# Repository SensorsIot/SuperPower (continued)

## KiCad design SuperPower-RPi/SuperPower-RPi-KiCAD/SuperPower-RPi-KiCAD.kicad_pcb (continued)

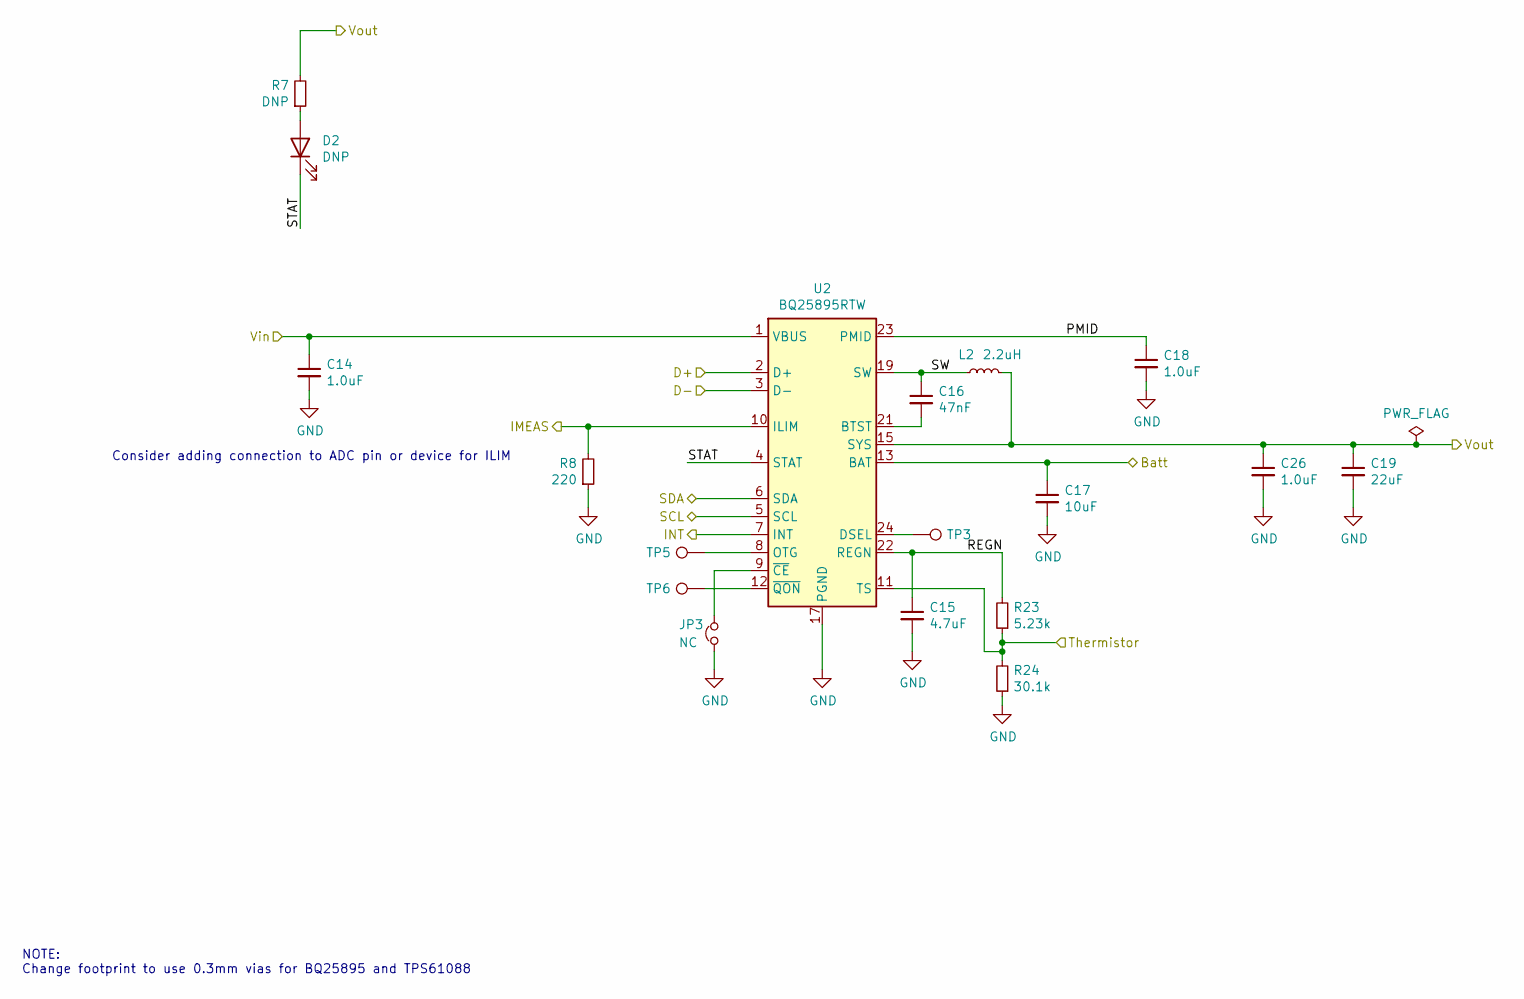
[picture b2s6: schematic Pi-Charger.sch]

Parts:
C14, C18, C26: 1.0uF; C_0402_1005Metric; Mfg PN GRM155R61E105KA12D; Digi-Key PN 490-10017-1-ND
C15: 4.7uF; C_0603_1608Metric; Mfg PN CL10A475KA8NQNC; Digi-Key PN 1276-1900-1-ND
C16: 47nF; C_0402_1005Metric; Mfg PN GRM155R71E473KA88D; Digi-Key PN 490-3254-1-ND
C17: 10uF; C_0805_2012Metric; Mfg PN GRM21BR61E106KA73L; Digi-Key PN 490-5523-1-ND
C19: 22uF; C_1206_3216Metric; Mfg PN CL31A226KAHNNNE; Digi-Key PN 1276-3047-1-ND
D2: DNP; LED_0603_1608Metric
JP3: NC; SolderJumper-2_P1.3mm_Bridged_Pad1.0x1.5mm
L2: 2.2uH; L_Vishay_IHLP-2525; Mfg PN IHLP2525CZER2R2M01; Digi-Key PN 541-1008-1-ND
R7: DNP; R_0603_1608Metric
R8: 220; R_0603_1608Metric; Mfg PN RC0603FR-07220RL; Digi-Key PN 311-220HRCT-ND
R23: 5.23k; R_0603_1608Metric; Mfg PN RC0603FR-075K23L; Digi-Key PN 311-5.23KHRCT-ND
R24: 30.1k; R_0603_1608Metric; Mfg PN RC0603FR-0730K1L; Digi-Key PN 311-30.1KHRCT-ND
TP3, TP5, TP6: DNP; TestPoint_Pad_1.0x1.0mm
U2: BQ25895RTW; Texas_S-PWQFN-N24_EP2.7x2.7mm_ThermalVias; Mfg PN BQ25895RTWR; Digi-Key PN 296-44345-1-ND

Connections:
/Pi-Batt/BATT: C17.1, U2.13 (BAT), U2.14 (BAT); also elsewhere on the board
/Pi-Batt/Thermistor: R23.1, R24.2, U2.11 (TS); also elsewhere on the board
/Pi-Boost-Conv/Vin: C19.1, C26.1, L2.2, R7.2, U2.15 (SYS), U2.16 (SYS); also elsewhere on the board
/Pi-Charger/D+: U2.2 (D+); also elsewhere on the board
/Pi-Charger/D-: U2.3 (D-); also elsewhere on the board
/Pi-Charger/IMEAS: R8.2, U2.10 (ILIM); also elsewhere on the board
/Pi-Charger/PMID: C18.1, U2.23 (PMID)
/Pi-Charger/REGN: C15.1, R23.2, U2.22 (REGN)
/Pi-Charger/STAT: D2.1 (K), U2.4 (STAT)
/Pi-Charger/SW: C16.1, L2.1, U2.19 (SW), U2.20 (SW)
/Pi-Charger/Vin: C14.1, U2.1 (VBUS); also elsewhere on the board
/Pi-MCU/Charger_INT: U2.7 (INT); also elsewhere on the board
/SCL: U2.5 (SCL); also elsewhere on the board
/SDA: U2.6 (SDA); also elsewhere on the board
GND: C14.2, C15.2, C17.2, C18.2, C19.2, C26.2, JP3.1, R8.1, R24.1, U2.17 (PGND), U2.18 (PGND), U2.25 (PGND); also elsewhere on the board
unnamed: C16.2, U2.21 (BTST)
unnamed: D2.2 (A), R7.1
unnamed: JP3.2, U2.9 (~CE)
unnamed: TP3.1, U2.24 (DSEL)
unnamed: TP5.1, U2.8 (OTG)
unnamed: TP6.1, U2.12 (~QON)

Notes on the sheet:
NOTE: Change footprint to use 0.3mm vias for BQ25895 and TPS61088
Consider adding connection to ADC pin or device for ILIM

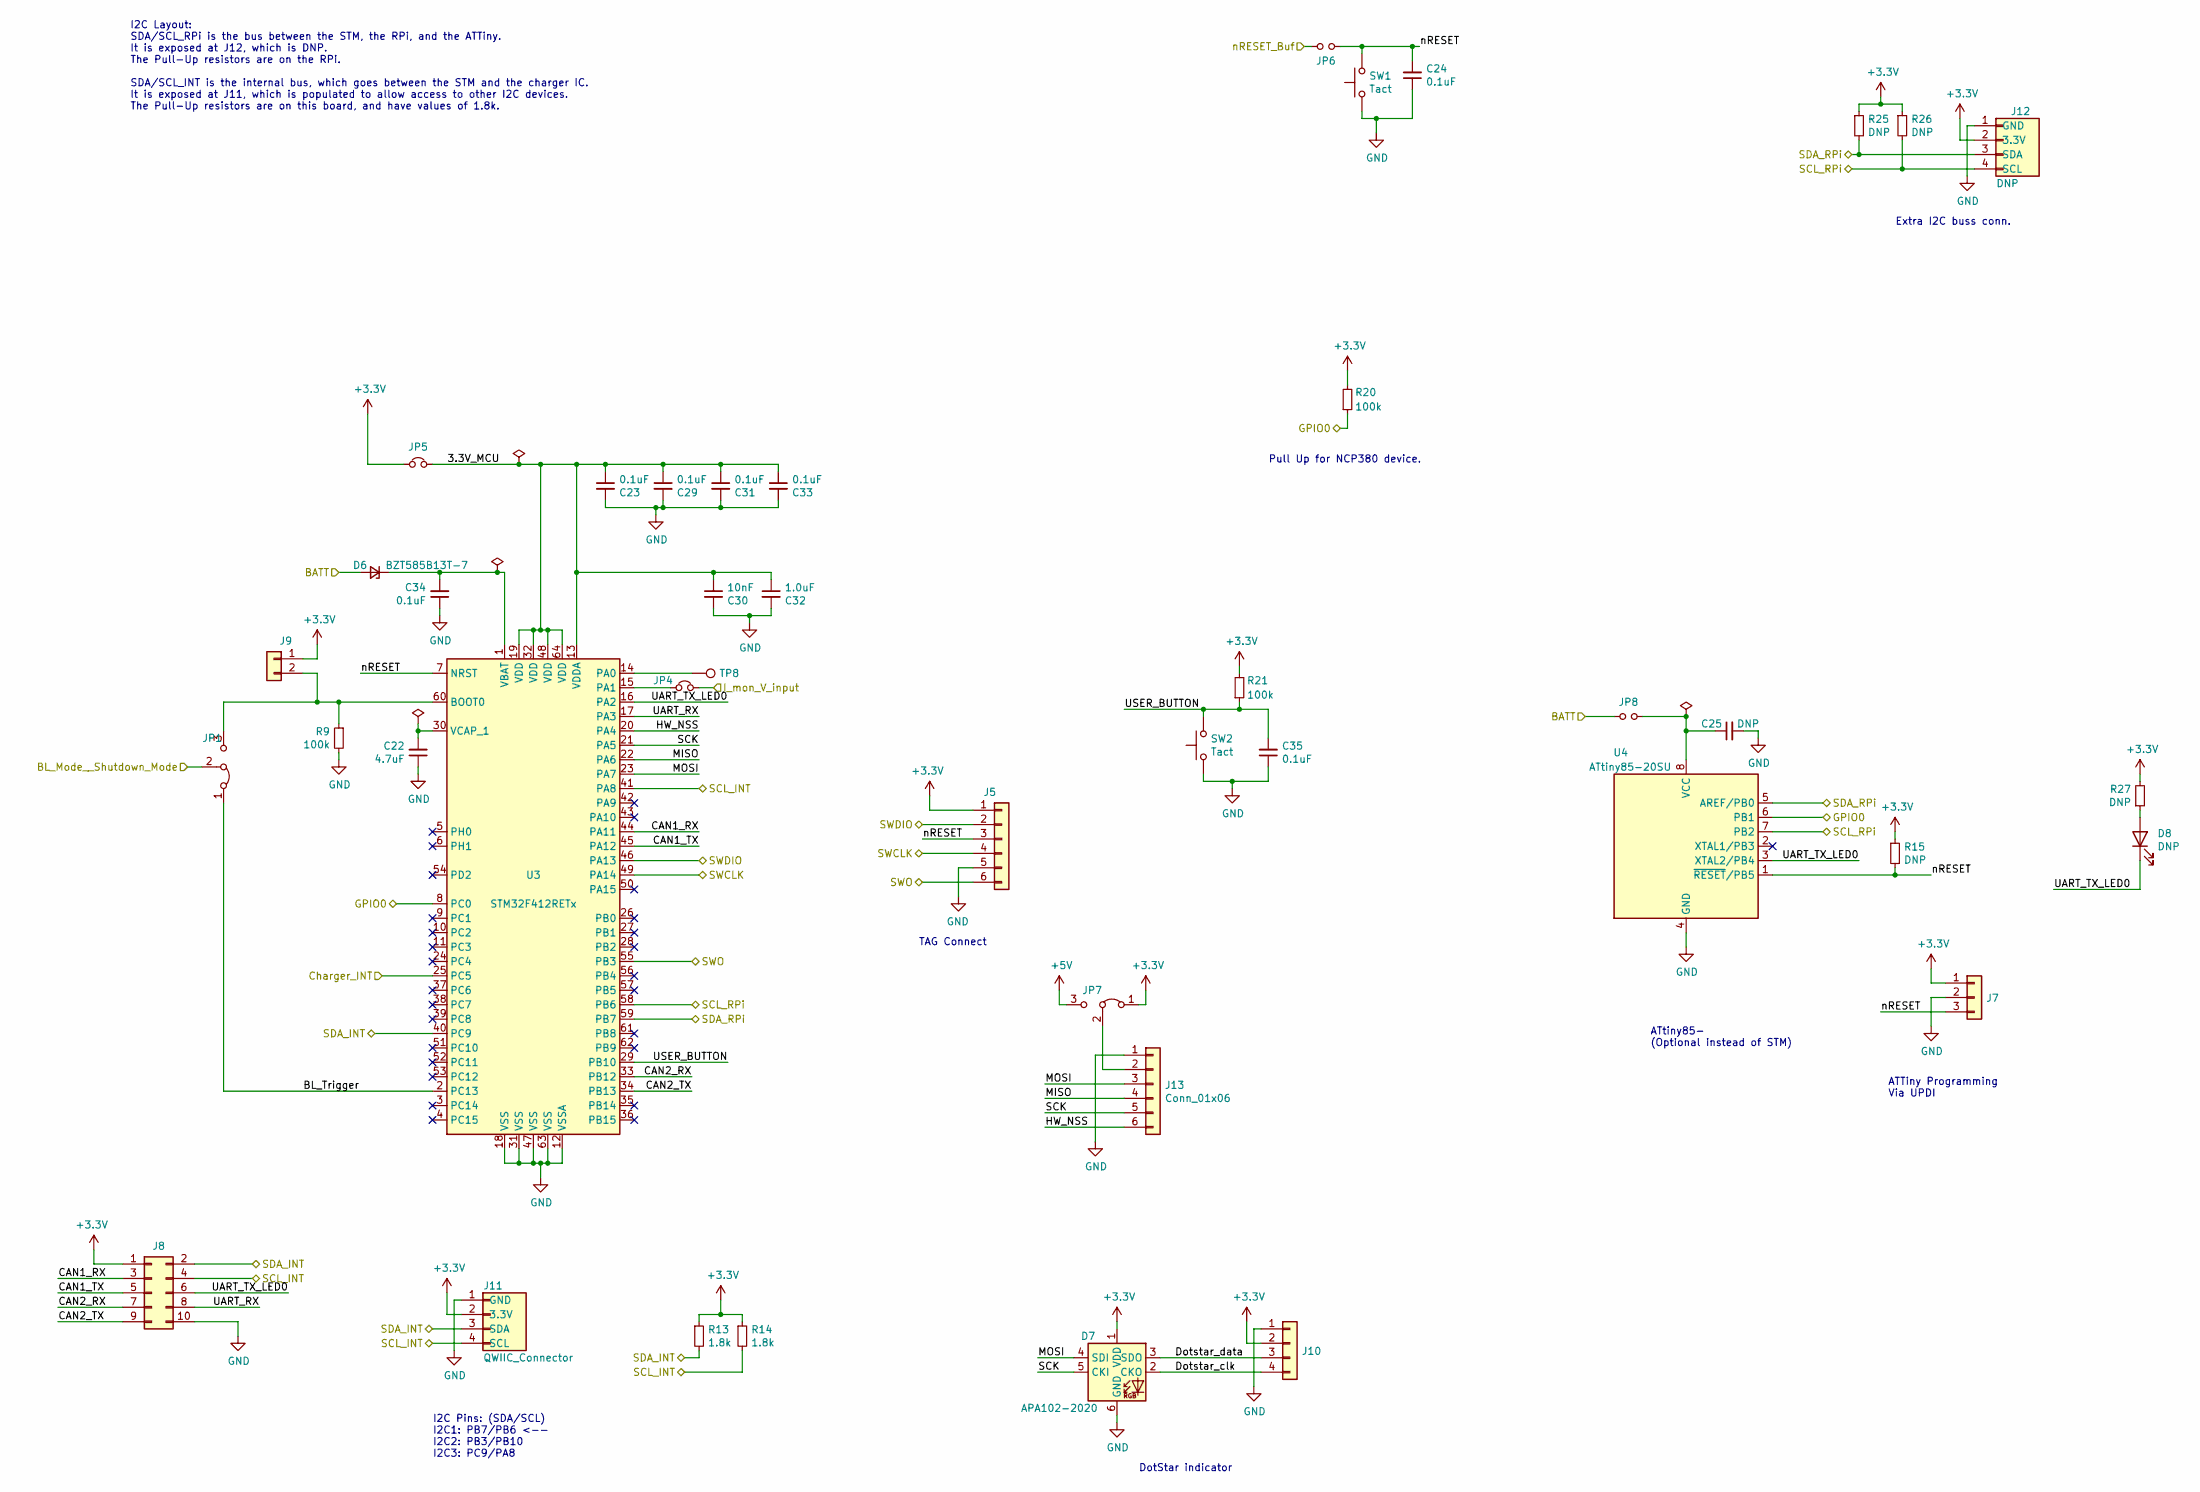
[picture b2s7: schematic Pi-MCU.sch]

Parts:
C22: 4.7uF; C_0603_1608Metric; Mfg PN CL10A475KA8NQNC; Digi-Key PN 1276-1900-1-ND
C23, C24, C29, C31, C33, C34, C35: 0.1uF; C_0402_1005Metric; Mfg PN TMK105BJ104KV-F; Digi-Key PN 587-1456-1-ND
C25: DNP; C_0603_1608Metric
C30: 10nF; C_0402_1005Metric; Mfg PN GCM155R71H103KA55D; Digi-Key PN 490-4762-1-ND
C32: 1.0uF; C_0402_1005Metric; Mfg PN GRM155R61E105KA12D; Digi-Key PN 490-10017-1-ND
D6: BZT585B13T-7; D_SOD-523; Mfg PN BZT585B13T-7; Digi-Key PN BZT585B13T-7DICT-ND
D7: APA102-2020; LED-APA102-2020
D8: DNP; LED_0603_1608Metric
J5: DNP; Tag-Connect_TC2030-IDC-NL_2x03_P1.27mm_Vertical; Mfg PN DNP
J7: Conn_01x03; PinHeader_1x03_P2.54mm_Vertical
J8: Conn_02x05_Odd_Even; PinHeader_2x05_P2.54mm_Vertical
J9: Conn_01x02; PinHeader_1x02_P2.54mm_Vertical
J10: Conn_01x04; PinHeader_1x04_P2.54mm_Vertical
J11: QWIIC_Connector; JST_SH_SM04B-SRSS-TB_1x04-1MP_P1.00mm_Horizontal; Mfg PN SM04B-SRSS-TB(LF)(SN); Digi-Key PN 455-1804-1-ND
J12: DNP; JST_SH_SM04B-SRSS-TB_1x04-1MP_P1.00mm_Horizontal; Mfg PN SM04B-SRSS-TB(LF)(SN); Digi-Key PN 455-1804-1-ND
J13: Conn_01x06; PinHeader_1x06_P2.54mm_Vertical
JP1, JP7: DNP; SolderJumper-3_P1.3mm_Bridged12_RoundedPad1.0x1.5mm_NumberL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
JP4: NC; SolderJumper-2_P1.3mm_Bridged_Pad1.0x1.5mm
JP5: Jumper_NC_Small; PinHeader_1x02_P2.54mm_Vertical_Shorted
JP6, JP8: Jumper_NO_Small; SolderJumper-2_P1.3mm_Open_Pad1.0x1.5mm
R9, R20, R21: 100k; R_0402_1005Metric; Mfg PN RC0402FR-07100KL; Digi-Key PN 311-100KLRCT-ND
R13, R14: 1.8k; R_0603_1608Metric; Mfg PN RC0603FR-071K8L; Digi-Key PN 311-1.80KHRCT-ND
R15, R25, R26, R27: DNP; R_0603_1608Metric
SW1, SW2: Tact; SW_Push_1P1T-SH_NO_CK_KMR2xxG; Mfg PN KMR221GLFS; Digi-Key PN 401-1427-1-ND
TP8: DNP; TestPoint_Pad_1.0x1.0mm
U3: STM32F412RETx; LQFP-64_10x10mm_P0.5mm; Mfg PN STM32F412RET6; Digi-Key PN 497-19350-1-ND
U4: ATtiny85-20SU; SOIJ-8_5.3x5.3mm_P1.27mm

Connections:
+3V3: D7.1 (VDD), J5.1, J7.1, J8.1, J9.1, J10.2, J11.2 (3.3V), J12.2 (3.3V), JP5.1, JP7.1 (A), R13.1, R14.1, R15.1, R20.2, R21.2, R25.1, R26.1, R27.2; also elsewhere on the board
+5V: JP7.3 (B); also elsewhere on the board
/Pi-Batt/BATT: D6.2 (A), JP8.2; also elsewhere on the board
/Pi-Charger/IMEAS: JP4.2; also elsewhere on the board
/Pi-Connection/GPIO4: JP6.1; also elsewhere on the board
/Pi-MCU/3.3V_MCU: C23.1, C29.1, C30.1, C31.1, C32.1, C33.1, JP5.2, U3.13 (VDDA), U3.19 (VDD), U3.32 (VDD), U3.48 (VDD), U3.64 (VDD)
/Pi-MCU/BL_Mode__Shutdown_Mode: JP1.2 (C); also elsewhere on the board
/Pi-MCU/BL_Trigger: JP1.1 (A), U3.2 (PC13)
/Pi-MCU/CAN1_RX: J8.3, U3.44 (PA11)
/Pi-MCU/CAN1_TX: J8.5, U3.45 (PA12)
/Pi-MCU/CAN2_RX: J8.7, U3.33 (PB12)
/Pi-MCU/CAN2_TX: J8.9, U3.34 (PB13)
/Pi-MCU/Charger_INT: U3.25 (PC5); also elsewhere on the board
/Pi-MCU/Dotstar_clk: D7.2 (CKO), J10.4
/Pi-MCU/Dotstar_data: D7.3 (SDO), J10.3
/Pi-MCU/GPIO0: R20.1, U3.8 (PC0), U4.6 (PB1); also elsewhere on the board
/Pi-MCU/HW_NSS: J13.6, U3.20 (PA4)
/Pi-MCU/MISO: J13.4, U3.22 (PA6)
/Pi-MCU/MOSI: D7.4 (SDI), J13.3, U3.23 (PA7)
/Pi-MCU/SCK: D7.5 (CKI), J13.5, U3.21 (PA5)
/Pi-MCU/SWCLK: J5.4, U3.49 (PA14); also elsewhere on the board
/Pi-MCU/SWDIO: J5.2, U3.46 (PA13); also elsewhere on the board
/Pi-MCU/SWO: J5.6, U3.55 (PB3); also elsewhere on the board
/Pi-MCU/UART_RX: J8.8, U3.17 (PA3)
/Pi-MCU/UART_TX_LED0: D8.1 (K), J8.6, U3.16 (PA2), U4.3 (XTAL2/PB4)
/Pi-MCU/USER_BUTTON: C35.2, R21.1, SW2.2, U3.29 (PB10)
/Pi-MCU/nRESET: C24.2, J5.3, J7.3, JP6.2, R15.2, SW1.2, U3.7 (NRST), U4.1 (~RESET~/PB5)
/SCL: J8.4, J11.4 (SCL), R14.2, U3.41 (PA8); also elsewhere on the board
/SCL_RPi: J12.4 (SCL), R26.2, U3.58 (PB6), U4.7 (PB2); also elsewhere on the board
/SDA: J8.2, J11.3 (SDA), R13.2, U3.40 (PC9); also elsewhere on the board
/SDA_RPi: J12.3 (SDA), R25.2, U3.59 (PB7), U4.5 (AREF/PB0); also elsewhere on the board
GND: C22.1, C23.2, C24.1, C25.2, C29.2, C30.2, C31.2, C32.2, C33.2, C34.1, C35.1, D7.6 (GND), J5.5, J7.2, J8.10, J10.1, J11.1 (GND), J12.1 (GND), J13.1, R9.2, SW1.1, SW2.1, U3.12 (VSSA), U3.18 (VSS), U3.31 (VSS), U3.47 (VSS), U3.63 (VSS), U4.4 (GND); also elsewhere on the board
unnamed: C22.2, U3.30 (VCAP_1)
unnamed: C25.1, JP8.1, U4.8 (VCC)
unnamed: C34.2, D6.1 (K), U3.1 (VBAT)
unnamed: D8.2 (A), R27.1
unnamed: J9.2, JP1.3 (B), R9.1, U3.60 (BOOT0)
unnamed: J13.2, JP7.2 (C)
unnamed: JP4.1, U3.15 (PA1)
unnamed: TP8.1, U3.14 (PA0)

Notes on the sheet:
I2C Pins: (SDA/SCL) I2C1: PB7/PB6 <-- I2C2: PB3/PB10 I2C3: PC9/PA8
TAG Connect
ATtiny85- (Optional instead of STM)
ATTiny Programming Via UPDI
Extra I2C buss conn.
DotStar indicator
I2C Layout: SDA/SCL_RPi is the bus between the STM, the RPi, and the ATTiny. It is exposed at J12, which is DNP. The Pull-Up resistors are on the RPi. SDA/SCL_INT is the internal bus, which goes between the STM and the charger IC. It is exposed at J11, which is populated to allow access to other I2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
Pull Up for NCP380 device.

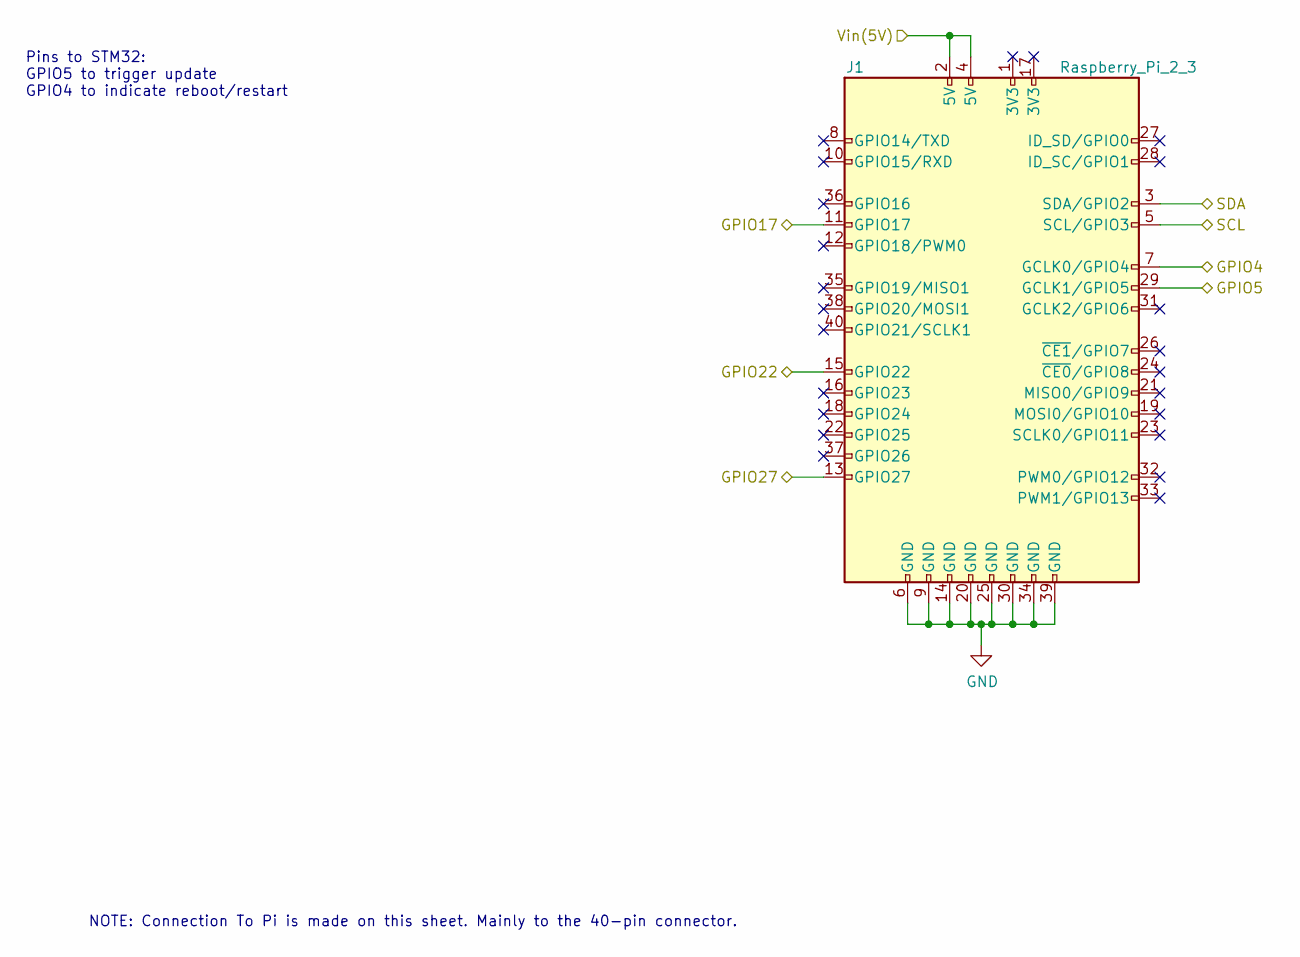
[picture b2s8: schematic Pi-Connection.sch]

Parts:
J1: Raspberry_Pi_2_3; PinSocket_2x20_P2.54mm_Vertical_With_Pogo

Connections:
/Pi-Connection/GPIO4: J1.7 (GCLK0/GPIO4); also elsewhere on the board
/Pi-Connection/GPIO17: J1.11 (GPIO17); also elsewhere on the board
/Pi-Connection/GPIO22: J1.15 (GPIO22); also elsewhere on the board
/Pi-Connection/GPIO27: J1.13 (GPIO27); also elsewhere on the board
/Pi-Connection/Vin(5V): J1.2 (5V), J1.4 (5V); also elsewhere on the board
/Pi-MCU/BL_Mode__Shutdown_Mode: J1.29 (GCLK1/GPIO5); also elsewhere on the board
/SCL_RPi: J1.5 (SCL/GPIO3); also elsewhere on the board
/SDA_RPi: J1.3 (SDA/GPIO2); also elsewhere on the board
GND: J1.6 (GND), J1.9 (GND), J1.14 (GND), J1.20 (GND), J1.25 (GND), J1.30 (GND), J1.34 (GND), J1.39 (GND); also elsewhere on the board

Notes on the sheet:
NOTE: Connection To Pi is made on this sheet. Mainly to the 40-pin connector.
Pins to STM32: GPIO5 to trigger update GPIO4 to indicate reboot/restart

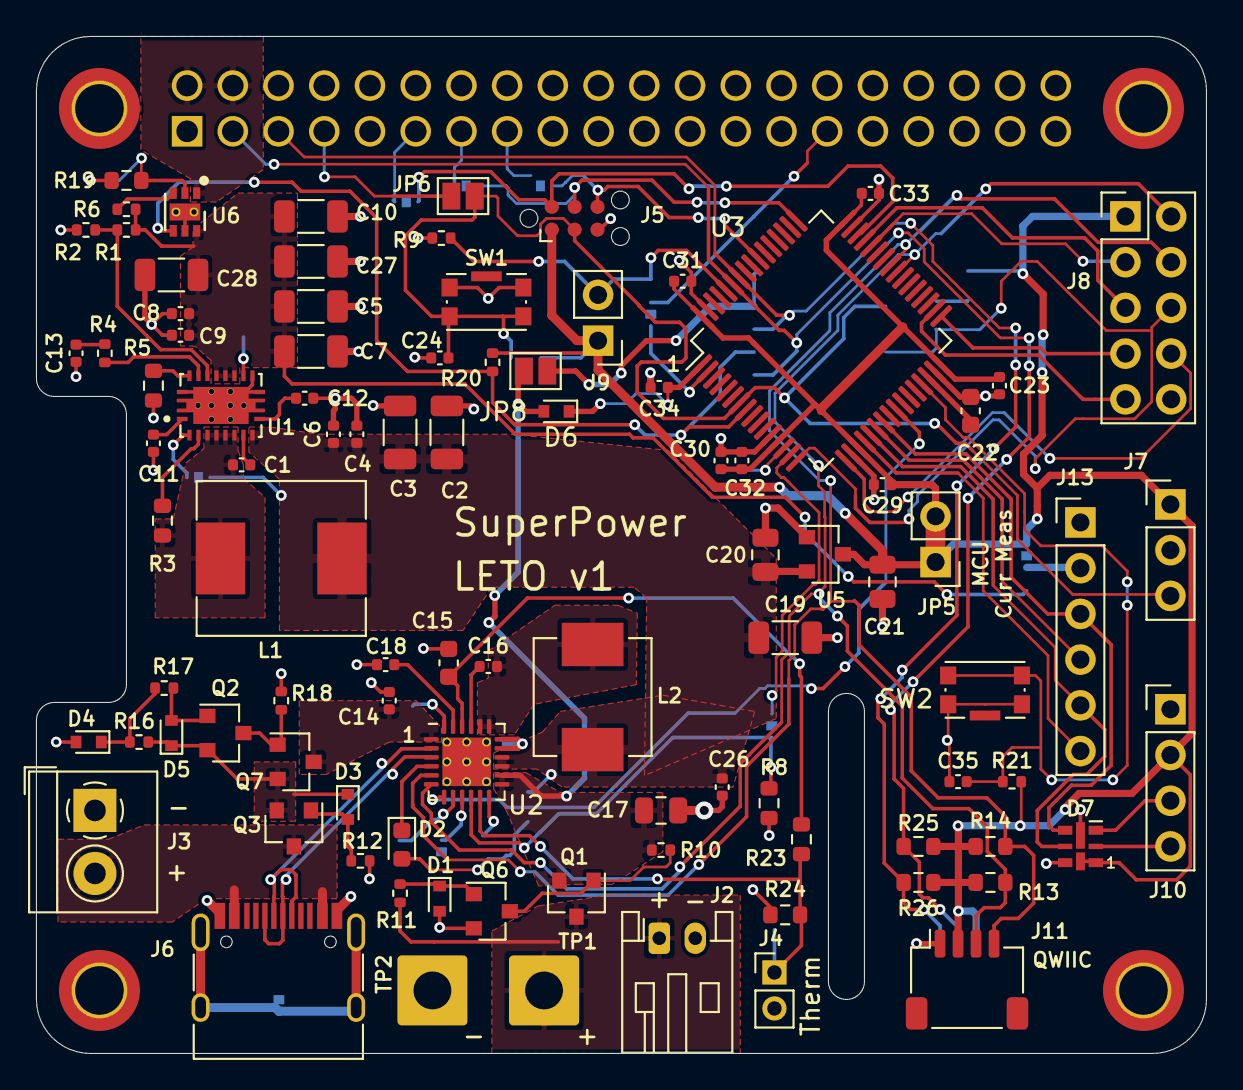
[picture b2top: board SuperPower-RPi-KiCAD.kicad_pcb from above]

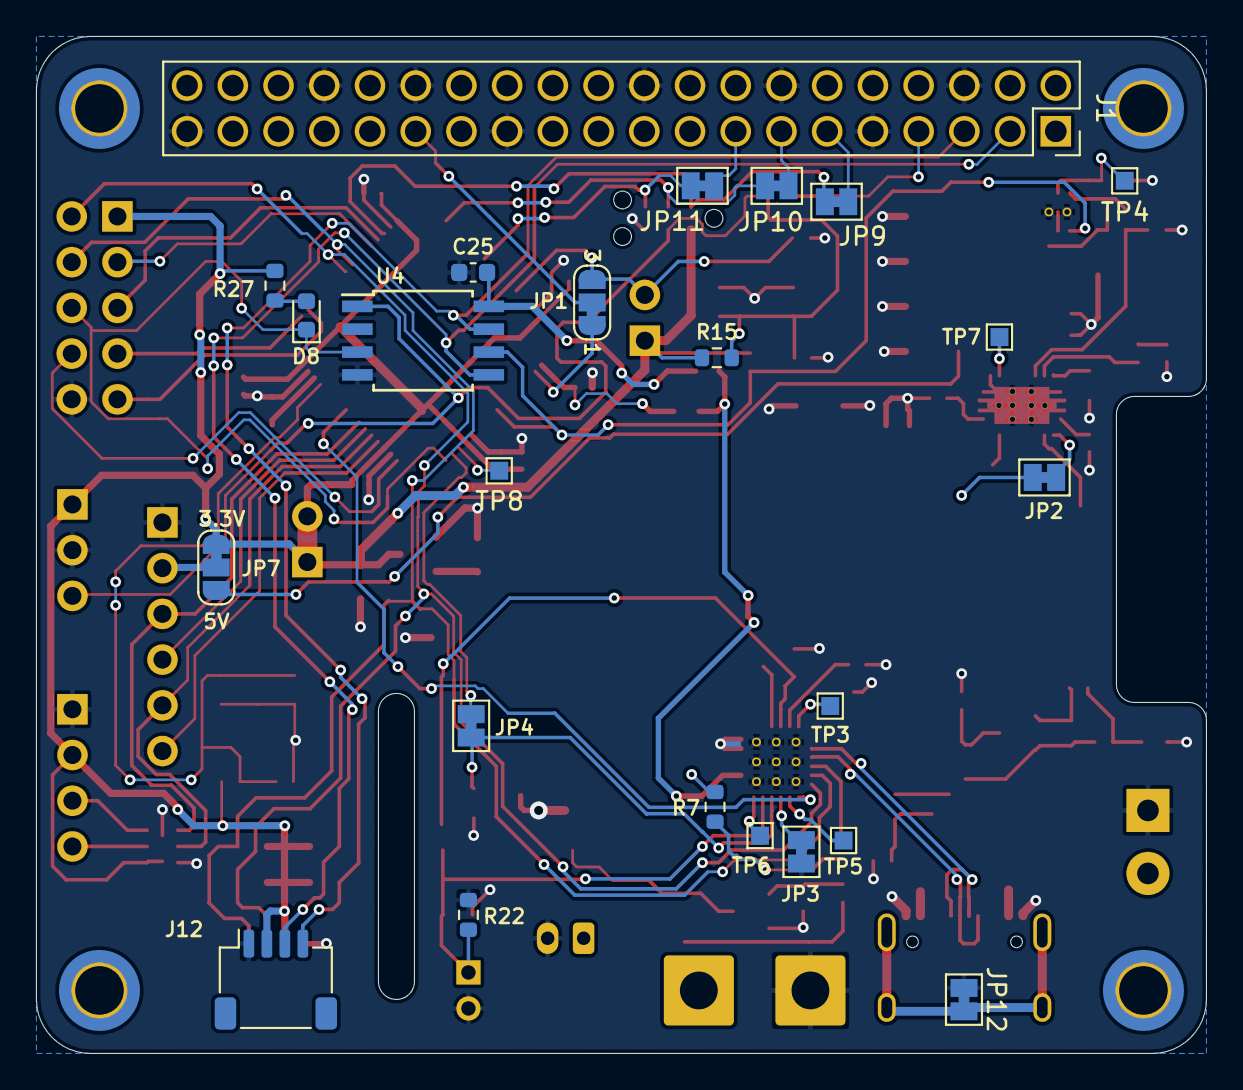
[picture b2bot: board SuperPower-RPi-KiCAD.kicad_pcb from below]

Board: 2 copper layers, 65.0 x 56.5 mm, 122 parts (24 on the bottom side), 82 nets.

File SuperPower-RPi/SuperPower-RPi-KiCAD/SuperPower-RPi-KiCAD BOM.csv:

Date:,1/9/2021 19:34,,,,
Tool:,Eeschema (5.1.8)-1,,,,
Component Count:,77,,,,
Ref,Qty,Value,Vendor,Vendor PN,Digi-Key PN
"C1, C6, C9, C23, C24, C29, C31, C33, C34, C35",10,0.1uF,Taiyo Yuden,TMK105BJ104KV-F,587-1456-1-ND
"C2, C3, C5, C7, C10, C19, C27, C28",8,22uF,Samsung,CL31A226KAHNNNE,1276-3047-1-ND
"C4, C8, C11, C14, C18, C26, C32",7,1.0uF,Murata Electronics,GRM155R61E105KA12D,490-10017-1-ND
"C12, C16",2,47nF,Murata,GRM155R71E473KA88D,490-3254-1-ND
C13,1,4700pF,Yageo,CC0402KRX7R8BB472,311-1039-1-ND
"C15, C22",2,4.7uF,Samsung,CL10A475KA8NQNC,1276-1900-1-ND
"C17, C20, C21",3,10uF,Murata,GRM21BR61E106KA73L,490-5523-1-ND
C30,1,10nF,Murata,GCM155R71H103KA55D,490-4762-1-ND
"D1, D3, D4, D5, D6",5,BZT585B13T-7,Diodes Incorporated,BZT585B13T-7,BZT585B13T-7DICT-ND
D7,1,APA102-2020,,,
J2,1,JST-PH,JST,S2B-PH-K-S(LF)(SN),
J6,1,USB_C_Receptacle_USB2.0,Korean Hroparts Elec,TYPE-C-31-M-12,
J11,1,QWIIC_Connector,JST,SM04B-SRSS-TB(LF)(SN),455-1804-1-ND
L1,1,1.2uH,Sumida,CDMC8D28NP-1R2MC,308-1618-1-ND
L2,1,2.2uH,Vishay-Dale,IHLP2525CZER2R2M01,541-1008-1-ND
"Q1, Q2, Q3, Q7",4,Q_PMOS_DMP3056L-7_SOT-23,Diodes Incorporated,DMP3056L-7,DMP3056L-7DICT-ND
Q6,1,2N7002-7-F,Diodes Incorporated,2N7002-7-F,2N7002-FDICT-ND
R1,1,324k,Panasonic Electronic Components,ERJ-2RKF3243X,P324KLCT-ND
"R2, R6, R9, R10, R11, R12, R16, R17, R18, R20, R21",11,100k,Yageo,RC0402FR-07100KL,311-100KLRCT-ND
R3,1,255k,Yageo,RC0603FR-07255KL,311-255KHRCT-ND
R4,1,17.4k,Yageo,RC0402FR-0717K4L,311-17.4KLRCT-ND
R5,1,100k,Yageo,RC0603FR-07100KL,311-100KHRCT-ND
R8,1,220,Yageo,RC0603FR-07220RL,311-220HRCT-ND
"R13, R14",2,1.8k,Yageo,RC0603FR-071K8L,311-1.80KHRCT-ND
R23,1,5.23k,Yageo,RC0603FR-075K23L,311-5.23KHRCT-ND
R24,1,30.1k,Yageo,RC0603FR-0730K1L,311-30.1KHRCT-ND
"SW1, SW2",2,Tact,C&K,KMR221GLFS,401-1427-1-ND
U1,1,TPS61088,Texas Instruments,TPS61088RHLR,296-43620-1-ND
U2,1,BQ25895RTW,Texas Instruments,BQ25895RTWR,296-44345-1-ND
U3,1,STM32F412RETx,ST,STM32F412RET6,497-19350-1-ND
U5,1,ME6210A33M3G,MicrOne,ME6210A33M3G,
U6,1,NCP380HMU21AATBG,On Semi,NCP380HMU21AATBG,NCP380HMU21AATBGOSCT-ND

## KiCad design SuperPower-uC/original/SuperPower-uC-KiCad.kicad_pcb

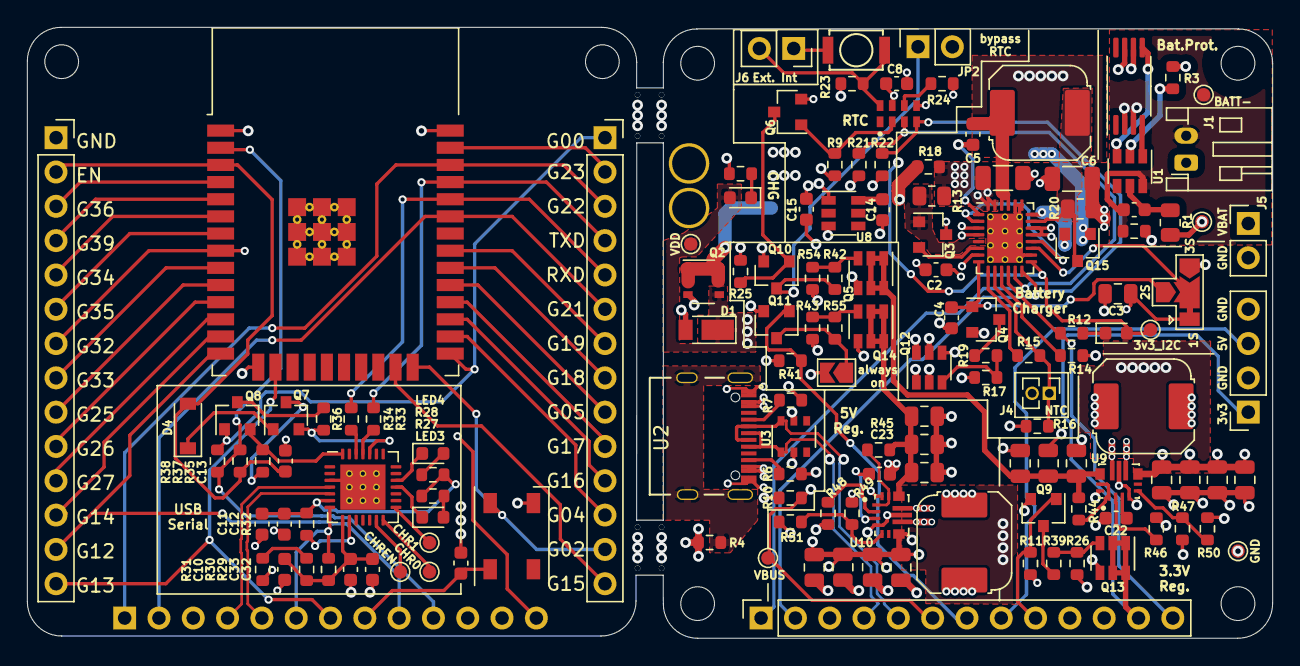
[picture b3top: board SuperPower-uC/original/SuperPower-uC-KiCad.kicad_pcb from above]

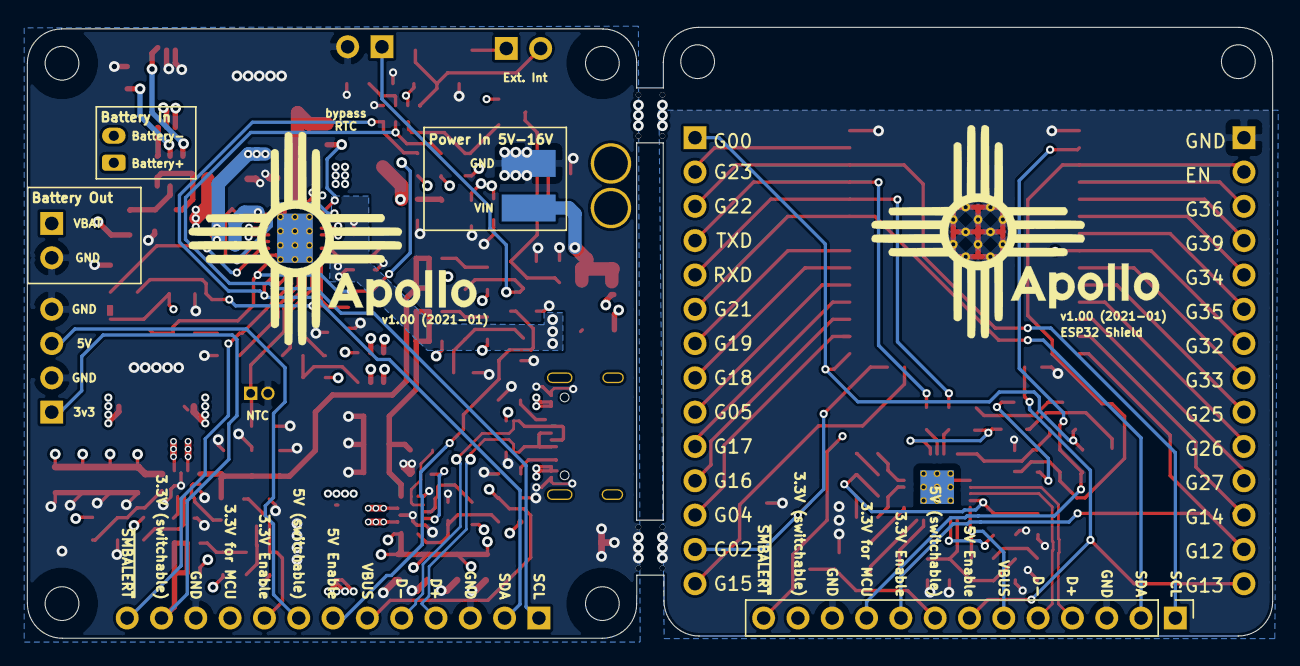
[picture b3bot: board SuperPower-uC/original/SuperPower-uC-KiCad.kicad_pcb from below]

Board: 4 copper layers, 92.2 x 45.2 mm, 148 parts (2 on the bottom side), 117 nets.

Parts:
C1, C2: CC0603JRX7R9BB104; C_0603_1608Metric
C3: TMK212AB7475KG-T; C_0805_2012Metric
C4: CL10B105KO8NNNC; C_0603_1608Metric
C5: CL10B223KB8NNNC; C_0603_1608Metric
C6, C7: CL31B106KAHNNNE; C_1206_3216Metric
C8, C9, C12, C22, C23, C33: 0.1µF; C_0603_1608Metric
C10, C11, C13: 1µF; C_0603_1608Metric
C14, C15: 2.2μF; C_0603_1608Metric
C16, C17, C18, C19, C20, C21, C24, C25: 10μF; C_0805_2012Metric
C26, C27, C28, C29, C30, C31: 22μF; C_0805_2012Metric
C32: 4.7µF; C_0603_1608Metric
D1: DFLS230L; D_PowerDI-123
D3: SK6812; LED_SK6812_PLCC4_5.0x5.0mm_P3.2mm
D4: B5819W; D_SOD-123
H1, H2, H3, H4, H5, H6: MountingHole; MountingHole_2.5mm
J1: JST_PH_S2B_thru; JST_PH_S2B-PH-K_1x02_P2.00mm_Horizontal
J3: Conn_01x02_Male; ext_input_pads
J4: DNP/JST_ZH_S2B_thru; PinHeader_1x02_P1.27mm_Vertical
J5: DNP/JST_XH_S2B_thru; PinHeader_1x02_P2.54mm_Vertical
J6: Conn_01x02_Male; PinSocket_1x02_P2.54mm_Vertical
J7, J8: Conn_01x14_Male; PinSocket_1x14_P2.54mm_Vertical
J9: Conn_01x13_Female; PinHeader_1x13_P2.54mm_Vertical
J10: Conn_01x13_Male; PinSocket_1x13_P2.54mm_Vertical
J11: Conn_01x04_Male; PinSocket_1x04_P2.54mm_Vertical
JP1: SolderJumper_4_Bridged_1C; SolderJumper-4_P2.0mm_Bridged1C_TrianglePad1.0x1.5mm_Number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
JP2: Jumper_NC_Small; PinSocket_1x02_P2.54mm_Vertical
JP3: Jumper_NC_Small; SolderJumper-2_P1.3mm_Open_TrianglePad1.0x1.5mm
L1: SPM6530T-4R7M; L_TDK_SPM6530T
L2, L3: SPM6530T-1R5M; L_TDK_SPM6530T
LED1: 150060VS75000_0603; LED_0603_1608Metric
LED2, LED3, LED4: 150060YS75000_0603; LED_0603_1608Metric
Q1: DMN2019UTS; TSSOP-8_4.4x3mm_P0.65mm
Q2: Si3421DV; TSOP-6_1.65x3.05mm_P0.95mm
Q3, Q15: DMN3023L; SOT-23
Q4, Q9, Q10, Q11: 2N7002A; SOT-23
Q5, Q12, Q13, Q14: DMP2035UVT; SOT-23-6
Q6: BSS84-7-F; SOT-23
Q7, Q8: S8050; SOT-23
R1: ERJ-P06F4700V; R_0805_2012Metric
R2, R4, R18: DNP/0; R_0603_1608Metric
R3: 2.7k; R_0603_1608Metric
R6, R7: 5.1k; R_0603_1608Metric
R8, R12: 2.2k; R_0603_1608Metric
R9, R19, R39, R54, R55: 390k; R_0603_1608Metric
R10, R35, R36, R37, R38: 12k; R_0603_1608Metric
R11, R17, R25, R26, R41, R42, R43: 1M; R_0603_1608Metric
R13, R20: RL0805FR-7W0R068L; R_0805_2012Metric
R14: 63.4k; R_0603_1608Metric
R15, R16, R24, R29, R30, R31, R44, R45: 10k; R_0603_1608Metric
R21, R22, R32: 4.7k; R_0603_1608Metric
R23, R46, R48: 100k; R_0603_1608Metric
R27, R28, R33, R34: 470; R_0603_1608Metric
R47: 150k; R_0603_1608Metric
R49: 130k; R_0603_1608Metric
R50: 470k; R_0603_1608Metric
R51: 680k; R_0603_1608Metric
SW1: DNP/SKRKAEE020; SKRKAEE020
TP1: VBAT; TestPoint_Pad_D1.0mm
TP2: BATT-; TestPoint_Pad_D1.0mm
TP3: GND; TestPoint_Pad_D1.0mm
TP4, TP5, TP29, TP30, TP31: TestPoint; TestPoint_Pad_D1.0mm
TP10: 3V3_I2C; TestPoint_Pad_D1.0mm
U1: AP9101CK6-AYTRG1; SOT-23-6
U2: USB-C; usb-c-usb4105
U3: IP4220CZ6; TSOP-6_1.65x3.05mm_P0.95mm
U4: LTC4162EUFD-LAD; QFN-28-1EP_4x5mm_P0.5mm_EP2.65x3.65mm_ThermalVias
U5: RV-3028-C7; IC_RV-3028-C7
U6: CP2102N-A01-GQFN28; QFN-28-1EP_5x5mm_P0.5mm_EP3.35x3.35mm_ThermalVias
U7: ESP32-WROOM32; ESP32-WROOM-32_EPAD_3x3_ThermalVias
U8: TPS70933DRVT; SOT-23-6
U9, U10: TPS63070RNMT; VREG_TPS63070RNMR

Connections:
-BATT: C1.2, J1.2, Q1.2, Q1.3, R2.2, TP2.1, U1.6
/3v3: J10.12, J11.1, Q13.1, Q13.2, Q13.5, Q13.6
/3v3_MCU: C24.1, C26.1, C28.1, C30.1, J10.10, Q13.4, R26.2, R46.2, R50.2, U9.7_8
/3v3_MCU_1: J9.10, R37.1, R38.1, U7.2
/5V: C25.1, C27.1, C29.1, C31.1, J10.8, J11.3, R48.2, R51.2, U10.7_8
/5V_1: C9.1, D3.3, J9.8
/Battery Module/VBAT: C6.1, J1.1, J5.1, R1.1, R20.1, TP1.1, U4.19, U4.20
/Charger inputs and USB IO/V_CHARGE: J3.1, Q2.1, Q2.2, Q2.5, Q2.6
/Charging Module/3v3_I2C: C8.2, C15.1, J6.1, LED2.2, Q6.2, R9.2, R21.1, R22.1, SW1.1, TP10.1, U4.15, U5.7, U8.1
/Charging Module/CELLS0: JP1.C, U4.17
/Charging Module/CELLS1: C3.1, JP1.1, U4.2, U4.18
/Charging Module/NTC: J4.1, R15.1, R16.2, U4.10
/Charging Module/NTCbias: R15.2, U4.9
/Charging Module/VCC2P5: C4.1, JP1.2, Q4.1, U4.8
/D1+: J9.4, U6.4
/D1-: J9.5, U6.5
/D+: J10.4, U2.A6, U2.B6, U3.1
/D-: J10.5, U2.A7, U2.B7, U3.6
/EN_3V3: J10.9, Q9.1, R11.2
/EN_3V3_1: J7.13, J9.9, U7.14
/EN_5V: J10.7, Q11.1, R41.2
/EN_5V_1: J7.14, J9.7, U7.16
/MCU Module/DTR: Q8.2, R35.2, U6.28
/MCU Module/EN: C13.2, D4.2, J7.2, R37.2, U7.3
/MCU Module/IO0: J8.1, Q8.1, R38.2, U7.25
/MCU Module/IO4: J8.12, U7.26
/MCU Module/IO5: J8.9, U7.29
/MCU Module/IO14: J7.12, U7.13
/MCU Module/IO15: J8.14, U7.23
/MCU Module/IO16: J8.11, U7.27
/MCU Module/IO17: J8.10, U7.28
/MCU Module/IO18: J8.8, U7.30
/MCU Module/IO19: J8.7, U7.31
/MCU Module/IO23: J8.2, U7.37
/MCU Module/IO25: J7.9, U7.10
/MCU Module/IO26: J7.10, U7.11
/MCU Module/IO27: J7.11, U7.12
/MCU Module/IO33: J7.8, U7.9
/MCU Module/IO34: J7.5, U7.6
/MCU Module/IO35: J7.6, U7.7
/MCU Module/IO36: J7.3, U7.4
/MCU Module/IO39: J7.4, U7.5
/MCU Module/RGBW_LED: D3.2, J8.13, U7.24
/MCU Module/RSTb: R32.2, U6.9
/MCU Module/RTS: Q7.2, R36.2, U6.24
/MCU Module/RXD: J8.5, R34.1, U7.34
/MCU Module/RXT: LED3.1, U6.18
/MCU Module/TXD: J8.4, R33.1, U7.35
/MCU Module/TXT: LED4.1, U6.19
/MCU Module/VIO: C11.1, C12.1, R27.1, R28.1, R32.1, U6.6
/RTC/EVI: J6.2, R23.1, SW1.2, U5.8
/RTC/INT: Q6.3, Q10.1, R25.2
/RTC/VIN: C14.1, U8.6
/RTC/~INT: Q6.1, R9.1, U5.2
/Regulator and Cut-Off Module/VIN: Q5.4, Q12.1, Q12.2, Q12.5, Q12.6, Q14.4, R18.1, R42.2, R43.2
/SCL: J10.1, R21.2, U4.13, U5.3
/SCL_1: J8.3, J9.1, U7.36
/SDA: J10.2, R22.2, U4.14, U5.4
/SDA_1: J8.6, J9.2, U7.33
/VBUS_1: J9.6, R29.1, U6.7
/~SMBALERT: J10.13, R12.1, U4.12
/~SMBALERT_1: J7.7, J9.13, U7.8
GND: C2.2, C3.2, C4.2, C6.2, C7.2, C8.1, C9.2, C10.2, C11.2, C12.2, C13.1, C14.2, C15.2, C16.2, C17.2, C18.2, C19.2, C20.2, C21.2, C22.2, C23.2, C24.2, C25.2, C26.2, C27.2, C28.2, C29.2, C30.2, C31.2, C32.2, C33.2, D3.1, J3.2, J4.2, J5.2, J7.1, J9.3, J9.11, J10.3, J10.11, J11.2, J11.4, JP1.3, JP2.2, JP3.2, Q1.6, Q1.7, Q4.2, Q9.2, Q10.2, Q11.2, R2.1, R3.2, R4.2, R6.2, R7.2, R8.2, R10.2, R11.1, R14.1, R16.1, R23.2, R24.1, R25.1, R31.2, R41.1, R47.1, R49.1, TP3.1, U2.A1, U2.A12, U2.B1, U2.B12, U3.2, U4.16, U4.23, U4.24, U4.29, U5.5, U6.3, U6.29, U7.1, U7.15, U7.38, U7.39, U8.3, U9.4, U9.10, U9.15, U10.4, U10.10, U10.15
unnamed: C1.1, R1.2, U1.5
unnamed: C5.1, U4.1
unnamed: C5.2, L1.1, U4.25, U4.26
unnamed: C10.1, C32.1, C33.1, R29.2, R30.1, U6.8
unnamed: C16.1, C17.1, C19.1, Q5.1, Q5.2, Q5.5, Q5.6, R44.2, U9.12_13
unnamed: C18.1, C20.1, C21.1, Q14.1, Q14.2, Q14.5, Q14.6, R45.2, U10.12_13
unnamed: C22.1, U9.3
unnamed: C23.1, U10.3
unnamed: D4.1, Q7.1
unnamed: JP2.1, Q10.3, R54.1
unnamed: JP3.1, Q11.3, R55.1
unnamed: L1.2, Q15.3, R20.2, U4.21
unnamed: L2.1, U9.9
unnamed: L2.2, U9.11
unnamed: L3.1, U10.9
unnamed: L3.2, U10.11
unnamed: LED1.1, R8.1
unnamed: LED2.1, R12.2
unnamed: LED3.2, R27.2
unnamed: LED4.2, R28.2
unnamed: Q1.4, U1.1
unnamed: Q1.5, U1.3
unnamed: Q3.1, R13.2, U4.5
unnamed: Q3.2, U4.6
unnamed: Q4.3, R19.2
unnamed: Q5.3, R42.1, R54.2
unnamed: Q7.3, R35.1
unnamed: Q8.3, R36.1
unnamed: Q9.3, R39.1
unnamed: Q12.3, R17.2, R19.1
unnamed: Q13.3, R26.1, R39.2
unnamed: Q14.3, R43.1, R55.2
unnamed: Q15.2, U4.22
unnamed: R3.1, U1.2
unnamed: R4.1, U2.S1
unnamed: R6.1, U2.B5
unnamed: R7.1, U2.A5
unnamed: R14.2, U4.11
unnamed: R24.2, U5.6
unnamed: R30.2, R31.1
unnamed: R33.2, U6.25
unnamed: R34.2, U6.26
unnamed: R44.1, U9.1, U9.14
unnamed: R45.1, U10.1, U10.14
unnamed: R46.1, U9.2
unnamed: R47.2, R50.1, U9.5
unnamed: R48.1, U10.2
unnamed: R49.2, R51.1, U10.5
unnamed: TP29.1, U6.13
unnamed: TP30.1, U6.15
unnamed: TP31.1, U6.14
VBUS: D1.2, J10.6, Q2.3, R10.1, TP4.1, U2.A4, U2.A9, U2.B4, U2.B9, U3.5
VCC: C7.1, Q12.4, Q15.1, R13.1, R17.1, R18.2, U4.3, U4.4, U4.27, U4.28
VDD: C2.1, D1.1, LED1.2, Q2.4, Q3.3, TP5.1, U4.7

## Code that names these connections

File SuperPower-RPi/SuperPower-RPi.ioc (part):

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Mcu.Name=STM32F412R(E-G)Tx
Mcu.Package=LQFP64
Mcu.UserName=STM32F412RGTx
PA0.Signal=ADCx_IN0
PA1.Signal=ADCx_IN1
PA11.Mode=CAN_Activate
PA11.Signal=CAN1_RX
PA12.Mode=CAN_Activate
PA12.Signal=CAN1_TX
PA13.Mode=Trace_Asynchronous_SW
PA13.Signal=SYS_JTMS-SWDIO
PA14.Mode=Trace_Asynchronous_SW
PA14.Signal=SYS_JTCK-SWCLK
PA2.Mode=Asynchronous
PA2.Signal=USART2_TX
PA3.Mode=Asynchronous
PA3.Signal=USART2_RX
PA4.Mode=NSS_Signal_Hard_Output
PA4.Signal=SPI1_NSS
PA5.Mode=Full_Duplex_Master
PA5.Signal=SPI1_SCK
PA6.Mode=Full_Duplex_Master
PA6.Signal=SPI1_MISO
PA7.Mode=Full_Duplex_Master
PA7.Signal=SPI1_MOSI
PA8.Mode=I2C
PA8.Signal=I2C3_SCL
PB12.Mode=CAN_Activate
PB12.Signal=CAN2_RX
PB13.Mode=CAN_Activate
PB13.Signal=CAN2_TX
PB3.Mode=Trace_Asynchronous_SW
PB3.Signal=SYS_JTDO-SWO
PB6.Mode=I2C
PB6.Signal=I2C1_SCL
PB7.Mode=I2C
PB7.Signal=I2C1_SDA
PC13.GPIOParameters=GPIO_Label
PC13.GPIO_Label=BOOT0_Alt
PC13.Signal=GPXTI13
PC5.Signal=GPXTI5
PC9.Mode=I2C
PC9.Signal=I2C3_SDA
board=custom
